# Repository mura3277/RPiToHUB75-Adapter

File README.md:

# Raspberry Pi 40 Pin GPIO to HUB75 Adapter Board

This PCB maps the Pi GPIO to the HUB75 header. The remaining pins are mapped to a 8-pin header to connect additional devices. It is intended this is used with the [RGB LED Matrix](https://github.com/hzeller/rpi-rgb-led-matrix/tree/master) library.

Pin mapping for the remaining pins from the Pi GPIO:
|Col 1     | Col 2    |
|----------|----------|
|GPIO 6    |GPIO 13   |
|5v Power  |GPIO 19   |
|GND       |GPIO 26   |

Pin mapping for IO header for the future input PCB:
|Col 1     | Col 2    |
|----------|----------|
|GPIO 12   |GPIO 1    |
|GPIO 20   |GPIO 16   |
|GND       |GPIO 21   |

# Change Log
## 7.0
-  Added 2 pin power header.
-  Added 4 pin STEMMA QT connector.
-  Changed the 6 pin IO to a smaller JST SH.
-  Changed the 6 pin GPIO to a low profile pin socket.
-  Adjusted layout to support RPi5 with 5-6mm heatsink

## 6.0
-  Went back to the regular HUB75 mapping as outlined by the rpi-rgb-led-matrix repo.
-  Dropped some pins from the GPIO passthrough (extra GND, 3.3v).

## 5.0
-  Added a right angled tilt sensor to the board, connected to a GPIO pin.

## 4.0
-  Added buzzer to the board connected to a GPIO pin.
-  Split off the dedicated input pins to a 6 pin IDC so it can easily be connected to a daughter board.

## 3.0
-  Added 3 pin fan header connected to a GPIO pin for cooling a pi within an enclosure.

## 2.0
-  Added solder jumper pads to support displays with or without the extra data line E.

## 1.0
- Initial Version.

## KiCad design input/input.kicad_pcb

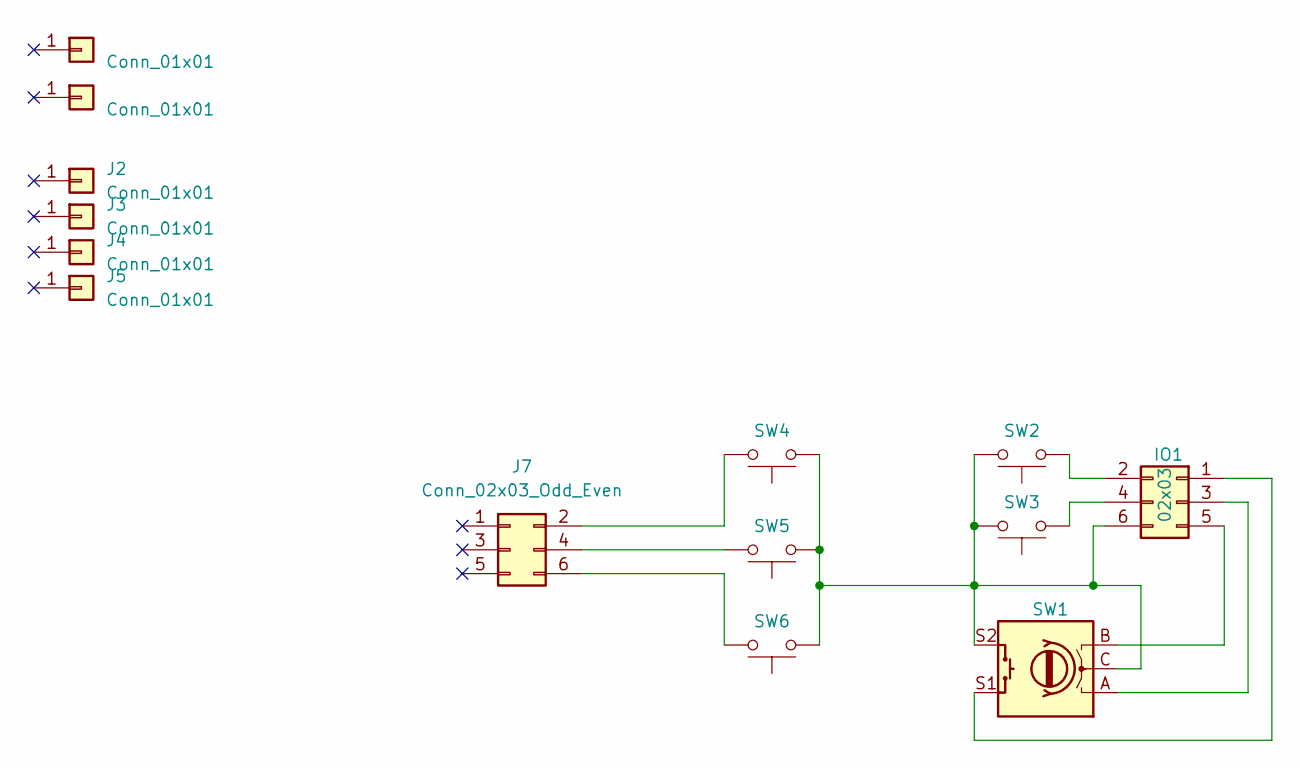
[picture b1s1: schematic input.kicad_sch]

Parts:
IO1: 02x03; JST_SH_SM06B-SRSS-TB_1x06-1MP_P1.00mm_Horizontal
J1: Conn_01x01; Breadboard
J2, J3, J4, J5: Conn_01x01; PinHeader_1x01_P2.54mm_Vertical
J6: Conn_01x01; raspberrypi_2_3
J7: Conn_02x03_Odd_Even; PinSocket_2x03_P2.54mm_Vertical
SW1: RotaryEncoder_Switch; RotaryEncoder_Alps_EC11E-Switch_Vertical_H20mm
SW2, SW3, SW4, SW5, SW6: SW_Push; SW_PUSH-12mm

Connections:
unnamed: IO1.1, SW1.S1
unnamed: IO1.2, SW2.1
unnamed: IO1.3, SW1.A
unnamed: IO1.4, SW3.1
unnamed: IO1.5, SW1.B
unnamed: IO1.6, SW1.C, SW1.S2, SW2.2, SW3.2, SW4.1, SW5.1, SW6.1
unnamed: J7.2, SW4.2
unnamed: J7.4, SW5.2
unnamed: J7.6, SW6.2

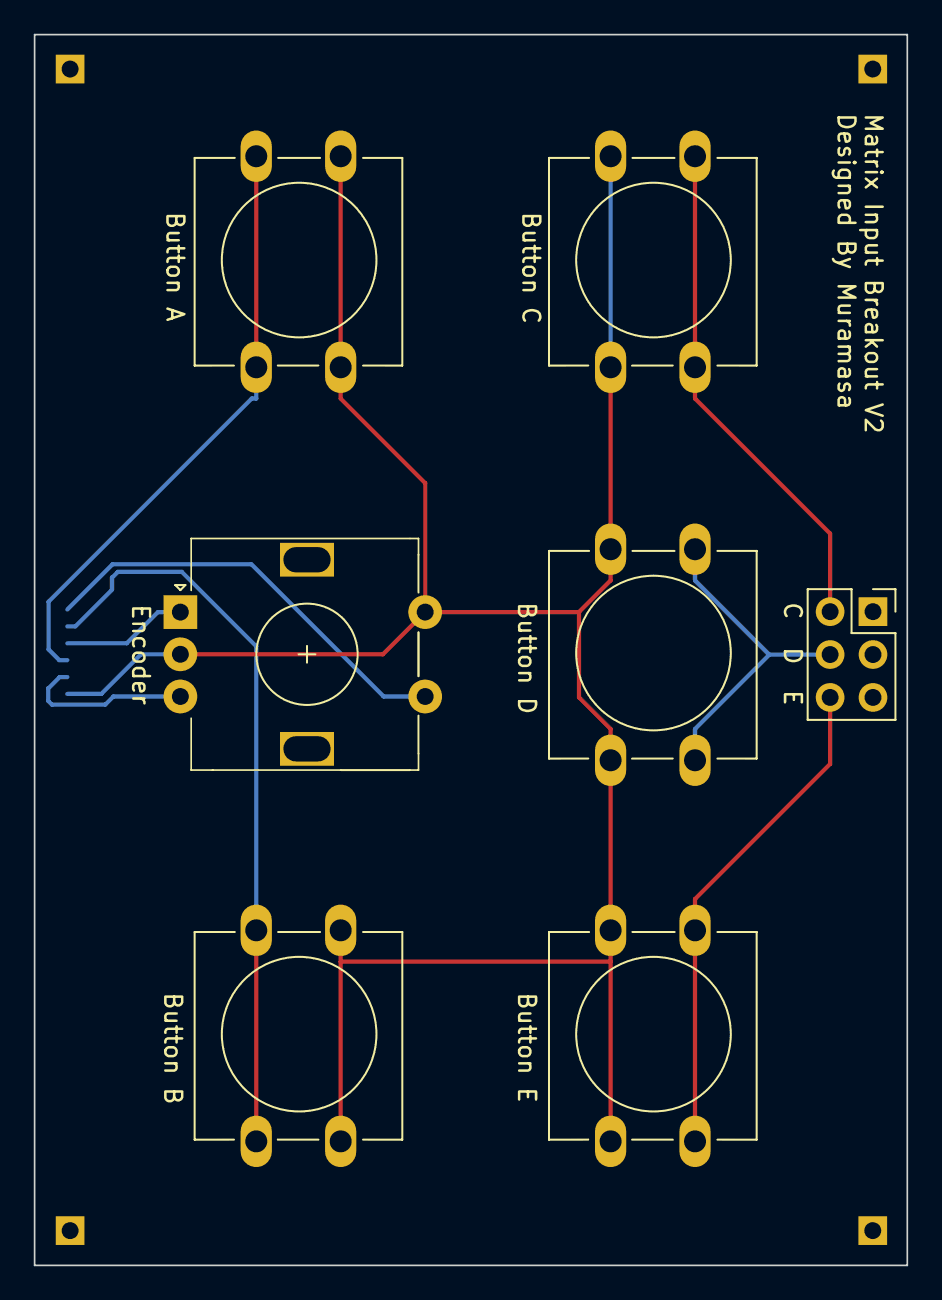
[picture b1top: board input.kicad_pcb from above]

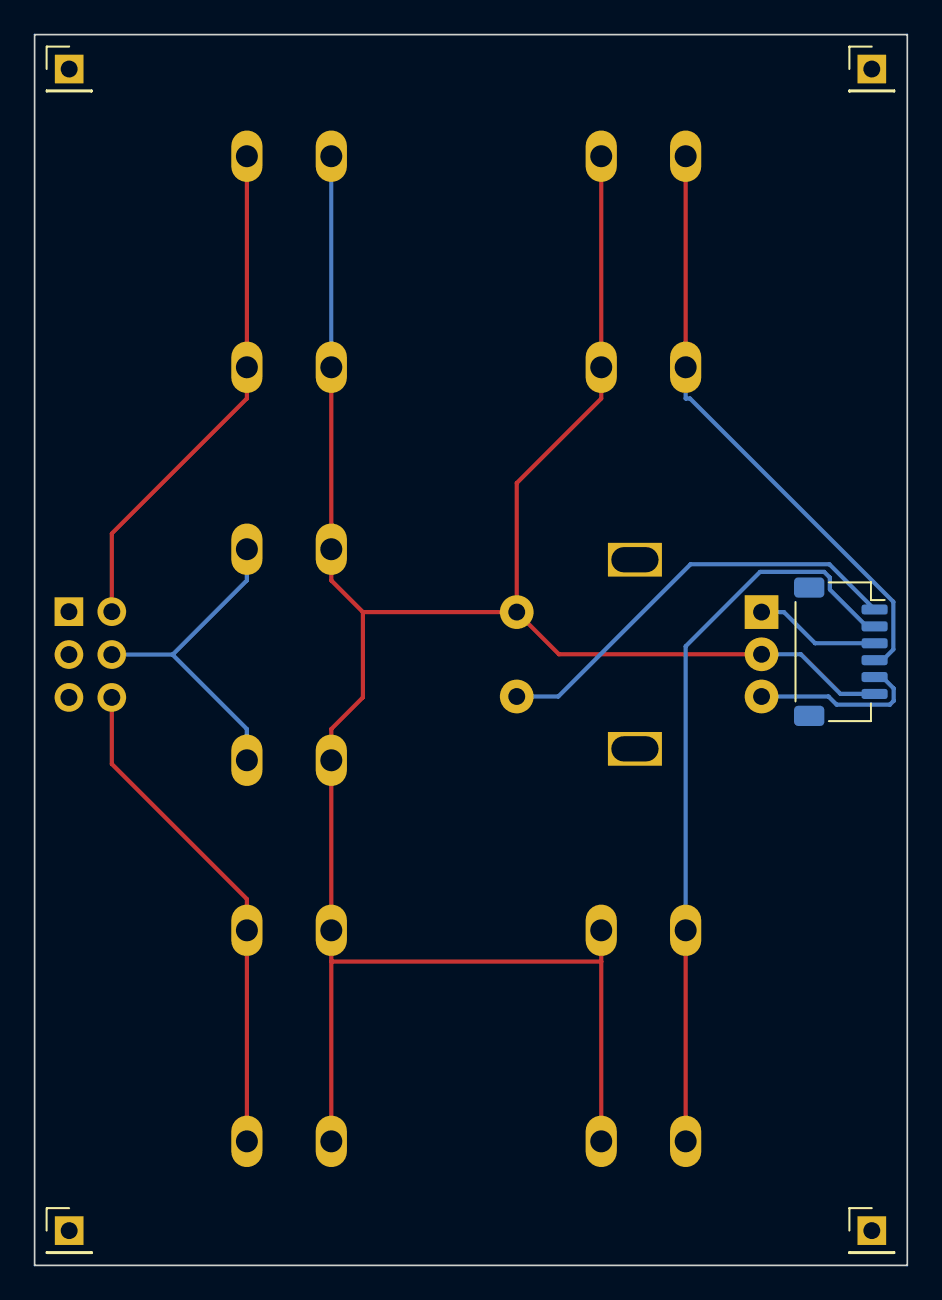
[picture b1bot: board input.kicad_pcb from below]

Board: 2 copper layers, 51.7 x 72.9 mm, 14 parts (6 on the bottom side), 9 nets.

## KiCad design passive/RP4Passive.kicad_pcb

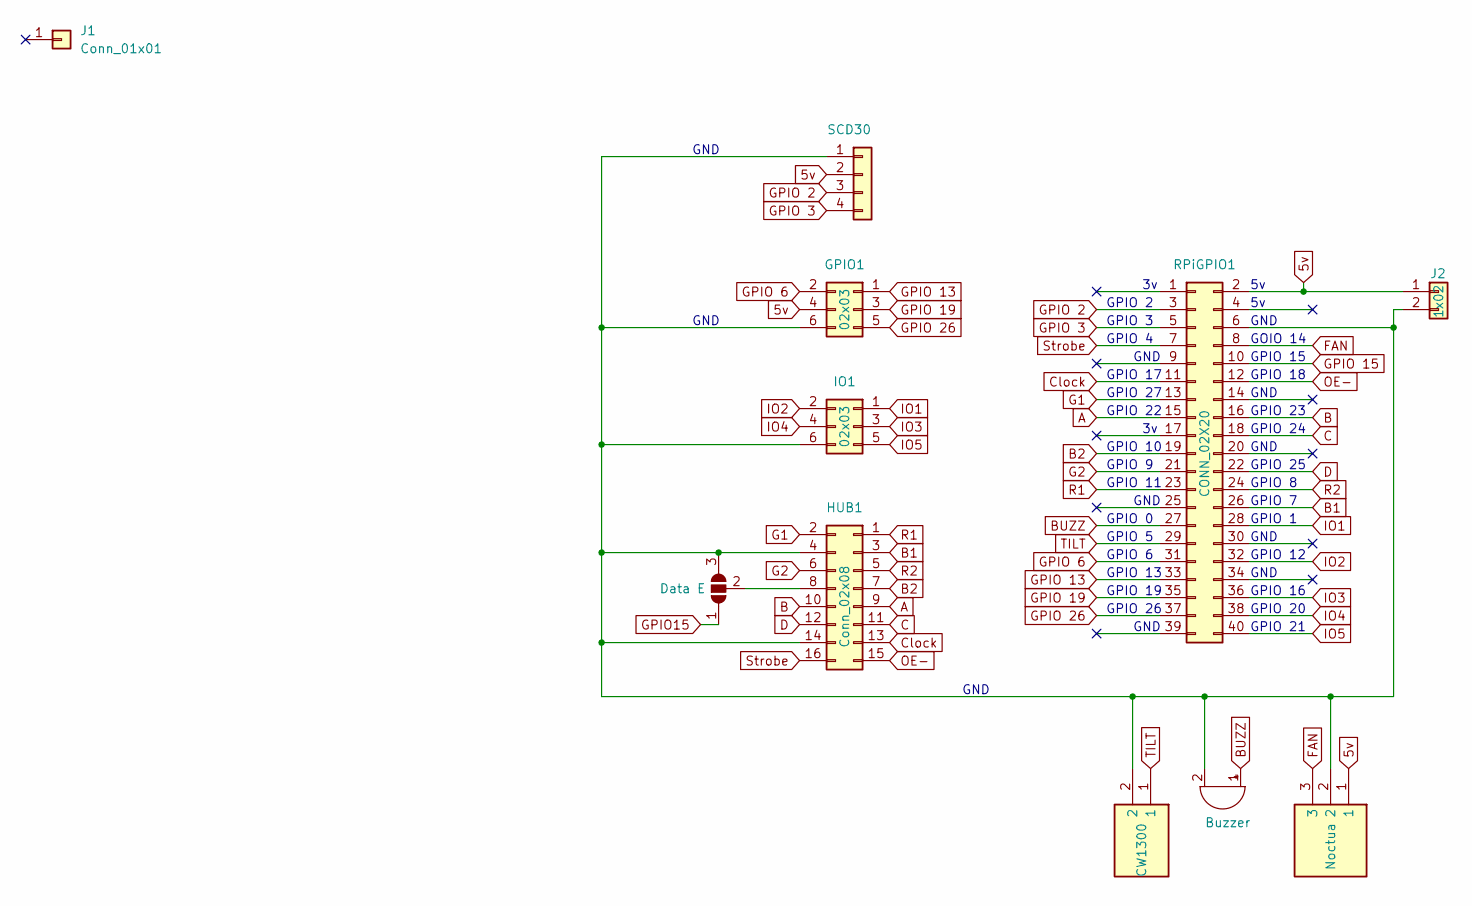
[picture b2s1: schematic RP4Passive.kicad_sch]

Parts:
BZ1: Buzzer; MagneticBuzzer_Kingstate_KCG0601
GPIO1: 02x03; GPIO Header
HUB1: Conn_02x08; HUB75
IO1: 02x03; JST_SH_SM06B-SRSS-TB_1x06-1MP_P1.00mm_Horizontal
J1: Conn_01x01; raspberrypi_2_3
J2: 1x02; JST_PH_S2B-PH-K_1x02_P2.00mm_Horizontal
JP1: Data E; SolderJumper-3_P1.3mm_Open_Pad1.0x1.5mm_NumberLabels
M1: Noctua; HDRRA3W64P0X254_1X3_747X318X635P; Mouser Part Number 538-171857-3003
RPiGPIO1: CONN_02X20; RPi GPIO
S1: CW1300; CW13001; Manufacturer_Part_Number CW1300-1
SCD30: Conn_01x04_Socket; STEMMA QT 1x04

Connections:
5v: GPIO1.4, J2.1, M1.1, RPiGPIO1.2, SCD30.2
A: HUB1.9, RPiGPIO1.15
B: HUB1.10, RPiGPIO1.16
B1: HUB1.3, RPiGPIO1.26
B2: HUB1.7, RPiGPIO1.19
BUZZ: BZ1.1 (-), RPiGPIO1.27
C: HUB1.11, RPiGPIO1.18
Clock: HUB1.13, RPiGPIO1.11
D: HUB1.12, RPiGPIO1.22
FAN: M1.3, RPiGPIO1.8
G1: HUB1.2, RPiGPIO1.13
G2: HUB1.6, RPiGPIO1.21
GPIO15: JP1.1 (A)
GPIO 2: RPiGPIO1.3, SCD30.3
GPIO 3: RPiGPIO1.5, SCD30.4
GPIO 6: GPIO1.2, RPiGPIO1.31
GPIO 13: GPIO1.1, RPiGPIO1.33
GPIO 15: RPiGPIO1.10
GPIO 19: GPIO1.3, RPiGPIO1.35
GPIO 26: GPIO1.5, RPiGPIO1.37
IO1: IO1.1, RPiGPIO1.28
IO2: IO1.2, RPiGPIO1.32
IO3: IO1.3, RPiGPIO1.36
IO4: IO1.4, RPiGPIO1.38
IO5: IO1.5, RPiGPIO1.40
unnamed: BZ1.2 (+), GPIO1.6, HUB1.4, HUB1.14, IO1.6, J2.2, JP1.3 (B), M1.2, RPiGPIO1.6, S1.2, SCD30.1
unnamed: HUB1.8, JP1.2 (C)
OE-: HUB1.15, RPiGPIO1.12
R1: HUB1.1, RPiGPIO1.23
R2: HUB1.5, RPiGPIO1.24
Strobe: HUB1.16, RPiGPIO1.7
TILT: RPiGPIO1.29, S1.1

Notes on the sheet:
GND
GPIO 22
GPIO 7
GPIO 12
GPIO 8
GPIO 16
GPIO 5
GPIO 23
GPIO 2
GPIO 11
GPIO 10
GPIO 27
GPIO 0
GPIO 4
GPIO 3
GND
GPIO 13
GOIO 14
GPIO 1
GPIO 21
GPIO 9
GPIO 26
GPIO 17
GPIO 24
GPIO 15
GPIO 18
GPIO 6
GPIO 19
GPIO 20
GPIO 25

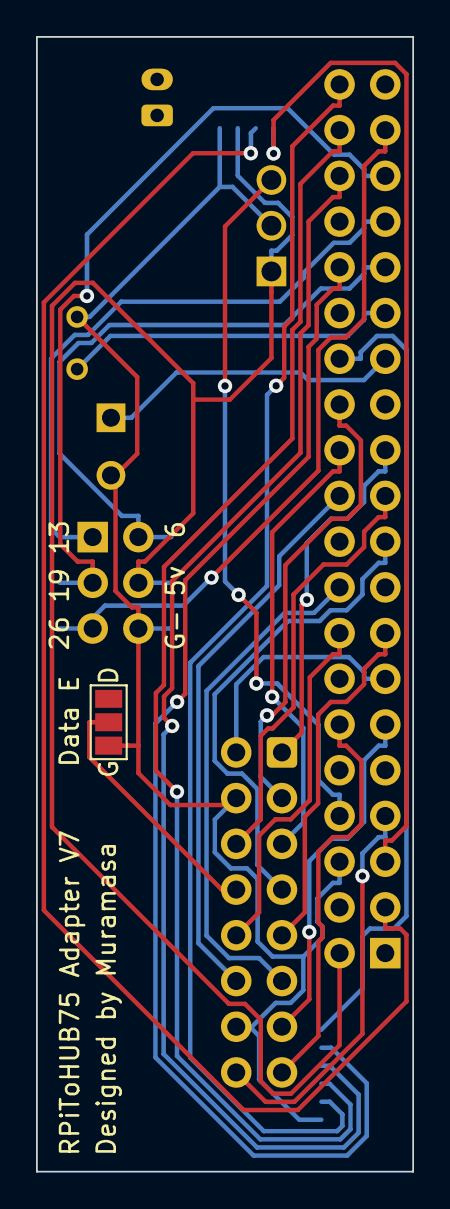
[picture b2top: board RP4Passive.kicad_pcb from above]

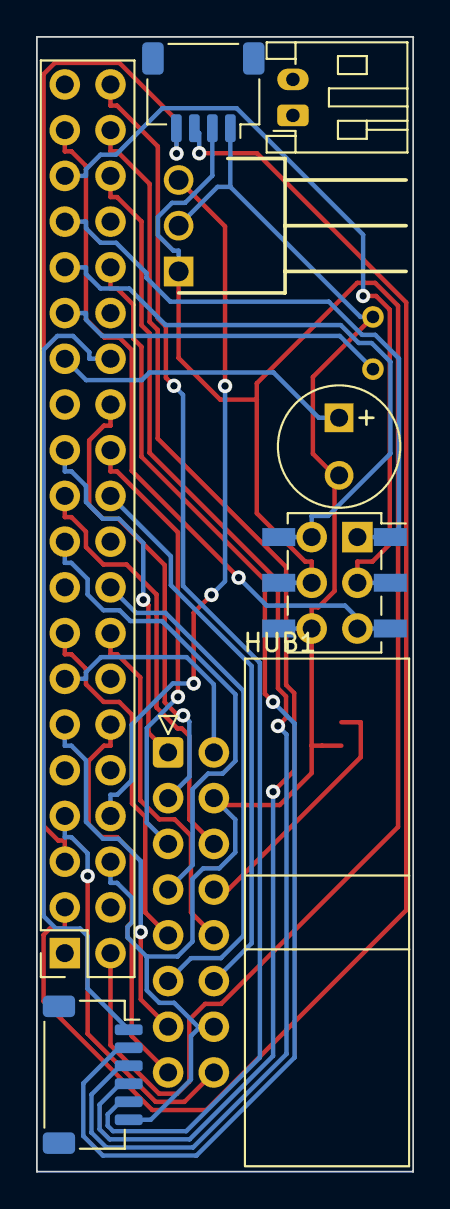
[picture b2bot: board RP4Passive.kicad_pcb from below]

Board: 2 copper layers, 20.9 x 63.0 mm, 11 parts (10 on the bottom side), 30 nets.

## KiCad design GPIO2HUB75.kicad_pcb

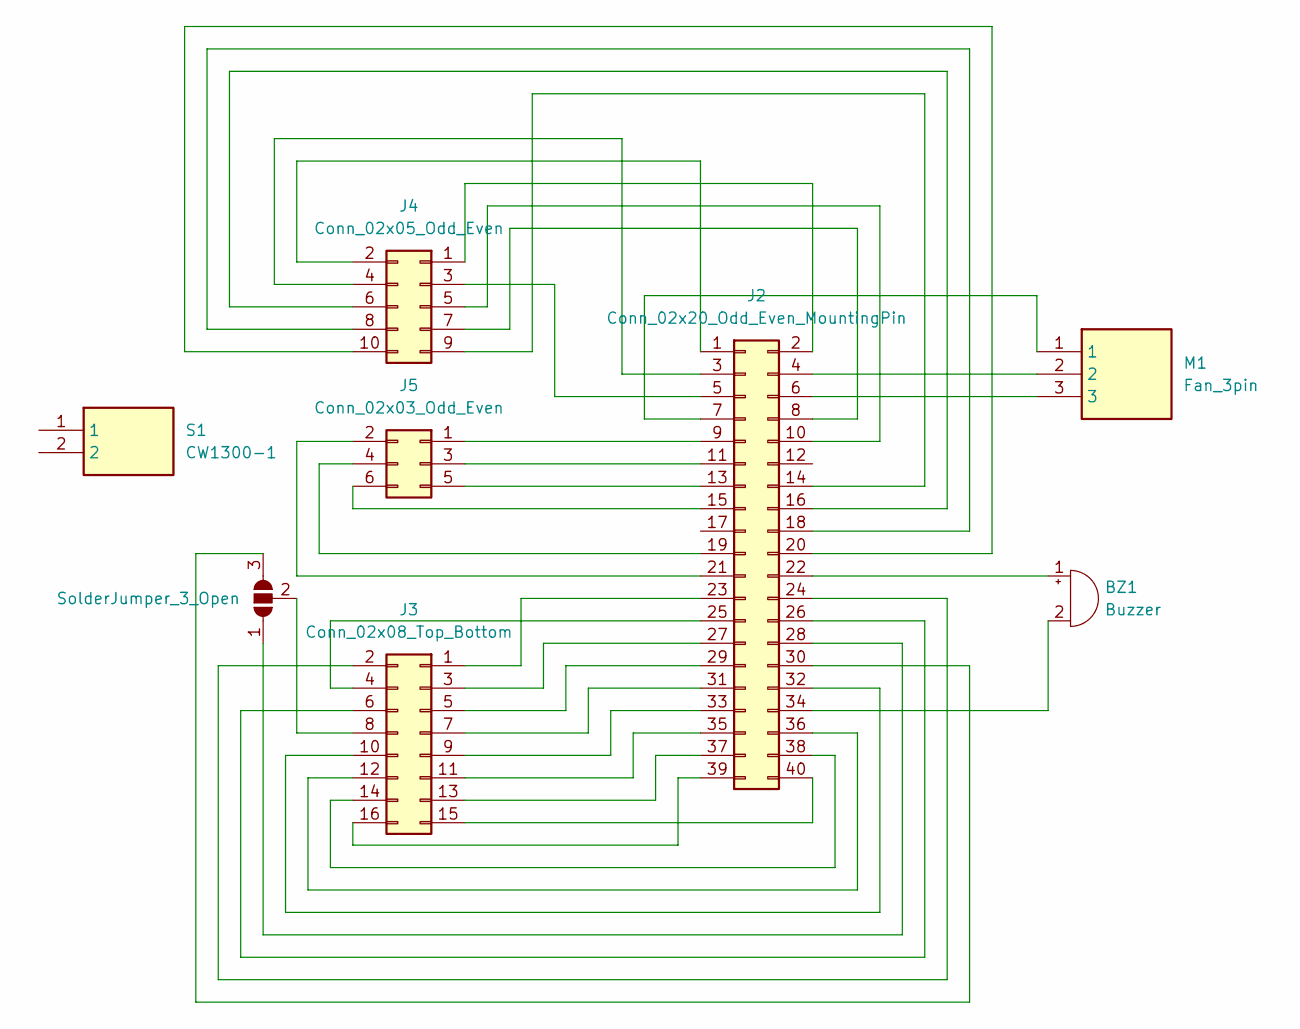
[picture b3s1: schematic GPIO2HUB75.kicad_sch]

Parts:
BZ1: Buzzer; MagneticBuzzer_Kingstate_KCG0601
J2: Conn_02x20_Odd_Even_MountingPin; PinSocket_2x20_P2.54mm_Vertical
J3: Conn_02x08_Top_Bottom; IDC-Header_2x08_P2.54mm_Horizontal
J4: Conn_02x05_Odd_Even; PinHeader_2x05_P2.54mm_Horizontal
J5: Conn_02x03_Odd_Even; IDC-Header_2x03_P2.54mm_Horizontal
JP1: SolderJumper_3_Open; SolderJumper-3_P1.3mm_Open_Pad1.0x1.5mm_NumberLabels
M1: Fan_3pin; HDRRA3W64P0X254_1X3_747X318X635P; Mouser Part Number 538-171857-3003
S1: CW1300-1; CW13001; Manufacturer_Part_Number CW1300-1

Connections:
unnamed: BZ1.2 (+), J2.34
unnamed: BZ1.1 (-), J2.22
unnamed: J2.1, J4.2
unnamed: J2.2, J4.1
unnamed: J2.3, J4.4
unnamed: J2.4, M1.2
unnamed: J2.5, J4.3
unnamed: J2.6, M1.3
unnamed: J2.7, M1.1
unnamed: J2.8, J4.7
unnamed: J2.9, J5.1
unnamed: J2.10, J4.5
unnamed: J2.11, J5.3
unnamed: J2.13, J5.5
unnamed: J2.14, J4.9
unnamed: J2.15, J5.6
unnamed: J2.16, J4.6
unnamed: J2.18, J4.8
unnamed: J2.19, J5.4
unnamed: J2.20, J4.10
unnamed: J2.21, J5.2
unnamed: J2.23, J3.1
unnamed: J2.24, J3.2
unnamed: J2.25, J3.4
unnamed: J2.26, J3.6
unnamed: J2.27, J3.3
unnamed: J2.28, JP1.1 (A)
unnamed: J2.29, J3.5
unnamed: J2.30, JP1.3 (B)
unnamed: J2.31, J3.7
unnamed: J2.32, J3.10
unnamed: J2.33, J3.9
unnamed: J2.35, J3.11
unnamed: J2.36, J3.12
unnamed: J2.37, J3.13
unnamed: J2.38, J3.14
unnamed: J2.39, J3.16
unnamed: J2.40, J3.15
unnamed: J3.8, JP1.2 (C)

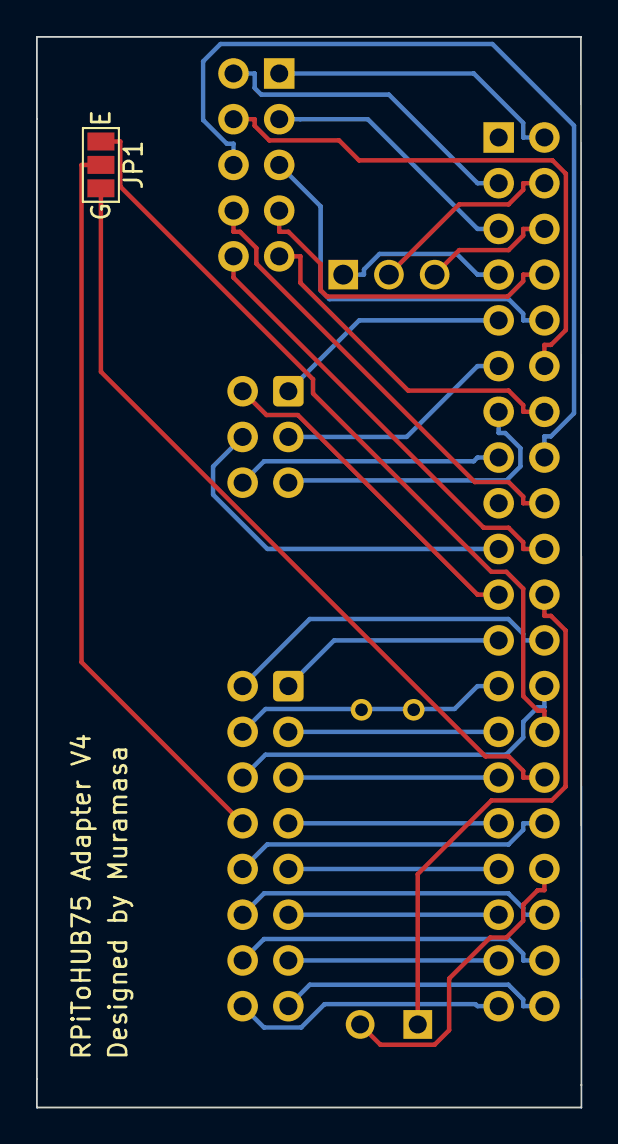
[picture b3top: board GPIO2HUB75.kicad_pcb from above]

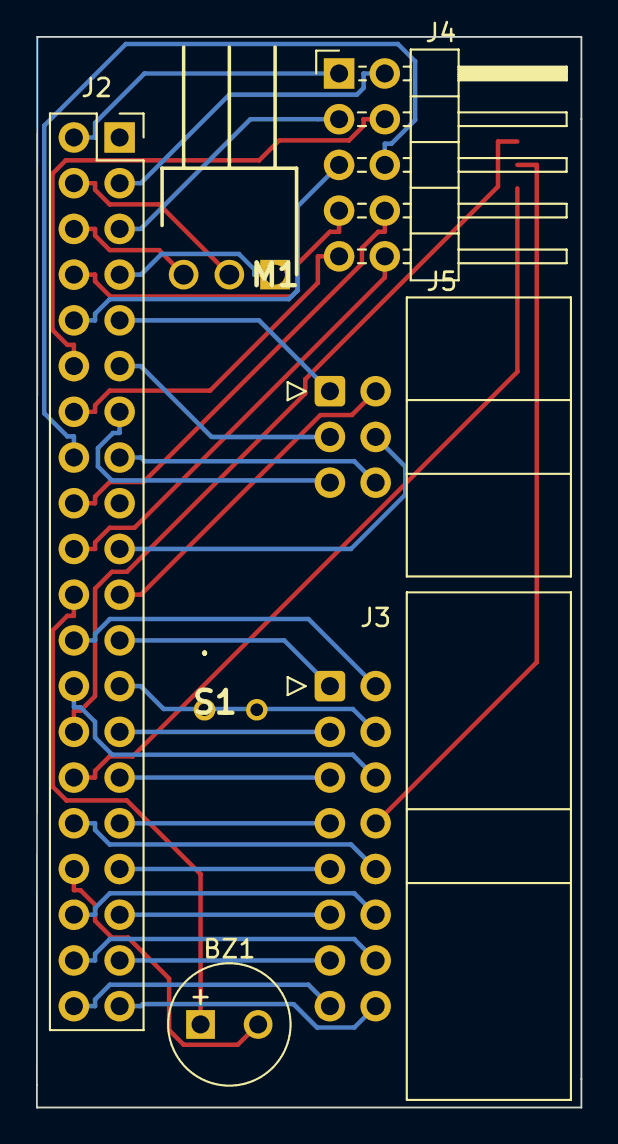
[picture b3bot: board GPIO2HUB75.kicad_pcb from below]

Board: 2 copper layers, 30.2 x 59.5 mm, 8 parts (7 on the bottom side), 39 nets.

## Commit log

2023-12-24 add files for version 1
2023-12-25 added solder bridge to support 64x64+ panels
2023-12-25 fix file
2023-12-25 move changes to readme
2023-12-25 added a 3pin fan header
2023-12-25 updated change log
2023-12-25 added a buzzer and split input pins from general GPIO
2023-12-25 update changelog
2023-12-26 added tilt sensor
2023-12-26 version 5
2023-12-26 folder restructure
2023-12-26 update readme to version 6
2023-12-26 update pin mapping to reflect rewire
2023-12-26 fix image
2023-12-26 add back 3.3v for the future co2 sensor
2023-12-26 update image
2023-12-27 version 7
2023-12-28 add input pcb breakout
